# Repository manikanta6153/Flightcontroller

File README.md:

# Flight Controller PCB

A custom-designed flight controller board built around the **STM32F407VGT6** microcontroller, featuring a full 10-DOF IMU sensor suite (accelerometer, gyroscope, barometer, magnetometer), USB-C connectivity, and 16 Mbit onboard flash storage. Designed in **KiCad 10.0**.

---

##  Board Preview

### PCB Layout (3D Render)

### Schematic

---

## Key Features

- **MCU:** STM32F407VGT6 — ARM Cortex-M4 @ 168 MHz, 1 MB Flash, 192 KB RAM (LQFP-100)
- **IMU:** Bosch BMI323 — 6-axis accelerometer + gyroscope (SPI)
- **Barometer:** Bosch BMP390L — high-precision pressure/altitude sensor
- **Magnetometer:** MEMSIC MMC5983MA — 3-axis magnetic field sensor
- **Flash Memory:** Winbond W25Q16JVSS — 16 Mbit SPI NOR flash
- **Power:** LD3985M33R — 3.3 V LDO voltage regulator (SOT-23-5)
- **Interface:** USB Type-C 2.0 (16-pin receptacle)
- **ESD Protection:** SMAJ5.0A TVS diode on power input
- **6× Motor / Servo outputs** via JST-XH 2-pin connectors
- **Debug / Peripheral headers:** 1×5 pin and 1×3 pin (2.00 mm pitch)
- **Status LED** and **2× Tactile switches** (BOOT / RESET)
- **Crystal oscillator** — SMD 2016 package (HSE for STM32)

---

## Connectors

| Ref | Connector | Type | Purpose |
|-----|-----------|------|---------|
| J1  | USB Type-C 16P | Palconn UTC16-G | USB 2.0 data + power |
| J2  | 1×05 Pin Header | 2.00 mm pitch | Debug / UART / SWD |
| J3  | 1×03 Pin Header | 2.00 mm pitch | Peripheral (e.g. GPS / RX) |
| J4–J9 | JST-XH 2-pin (×6) | 2.50 mm pitch | Motor / Servo / ESC outputs |

---

## PCB Specifications

| Parameter | Value |
|-----------|-------|
| Layers | 2 (F.Cu + B.Cu) |
| Board Thickness | 1.6 mm |
| Copper Thickness | 35 µm |
| Substrate | FR4 (εr = 4.5) |
| Smallest SMD Package | 0201 (0603 Metric) |
| Design Tool | KiCad 10.0.3 |

---

## Bill of Materials (Summary)

| Category | Components | Details |
|----------|------------|---------|
| MCU | U1 — STM32F407VGT6 | LQFP-100 |
| IMU | U2 — BMI323 | 6-axis accel + gyro |
| LDO | U3 — LD3985M33R | 3.3 V regulator |
| Barometer | U4 — BMP390L | Pressure / altitude |
| Magnetometer | U5 — MMC5983MA | 3-axis compass |
| Flash | U7 — W25Q16JVSS | 16 Mbit SPI NOR |
| Capacitors | C1–C23 (23 total) | 12 pF – 10 µF, 0402–0805 |
| Resistors | R1–R19 (17 total) | 22 Ω – 100 kΩ, 0201–0805 |
| Diodes | D1 (LED), D2 (TVS) | Status indicator + ESD |
| Crystal | Y1 | SMD 2016, 4-pin |
| Ferrite Bead | FB1 — 600 Ω | EMI filtering (0201) |
| Switches | SW1, SW2 | SPST tactile (BOOT / RESET) |
| Connectors | J1–J9 | USB-C, pin headers, JST-XH |

> **Total unique part count:** ~31 line items &nbsp;|&nbsp; **Total components:** ~65+

---

## Project Structure

```
Flightcontroller/
├── flight.kicad_pro          # KiCad project file
├── flight.kicad_sch          # Schematic
├── flight.kicad_pcb          # PCB layout
├── flight.kicad_prl          # Local project preferences
├── flight.csv                # BOM export
├── flight.xml                # Netlist / BOM XML export
├── place_footprints.log      # Footprint placement log
└── README.md                 # This file
```

---

## Getting Started

### Prerequisites
- [KiCad 10.0+](https://www.kicad.org/download/) installed

### Open the Project
1. Clone or download this repository
2. Open `flight.kicad_pro` in KiCad
3. Use the Schematic Editor to view/edit the circuit
4. Use the PCB Editor to view/edit the board layout

```bash
git clone https://github.com/manikanta6153/Flightcontroller.git
cd Flightcontroller
```

---

## Sensor Communication Interfaces

| Sensor | IC | Interface | Notes |
|--------|----|-----------|-------|
| Accel + Gyro | BMI323 | SPI | 6-axis IMU |
| Barometer | BMP390L | SPI / I²C | Altitude estimation |
| Magnetometer | MMC5983MA | SPI / I²C | Heading / compass |
| Flash | W25Q16JVSS | SPI | Blackbox / config storage |

---

## License

This is an open hardware project. See the repository for license details.

---

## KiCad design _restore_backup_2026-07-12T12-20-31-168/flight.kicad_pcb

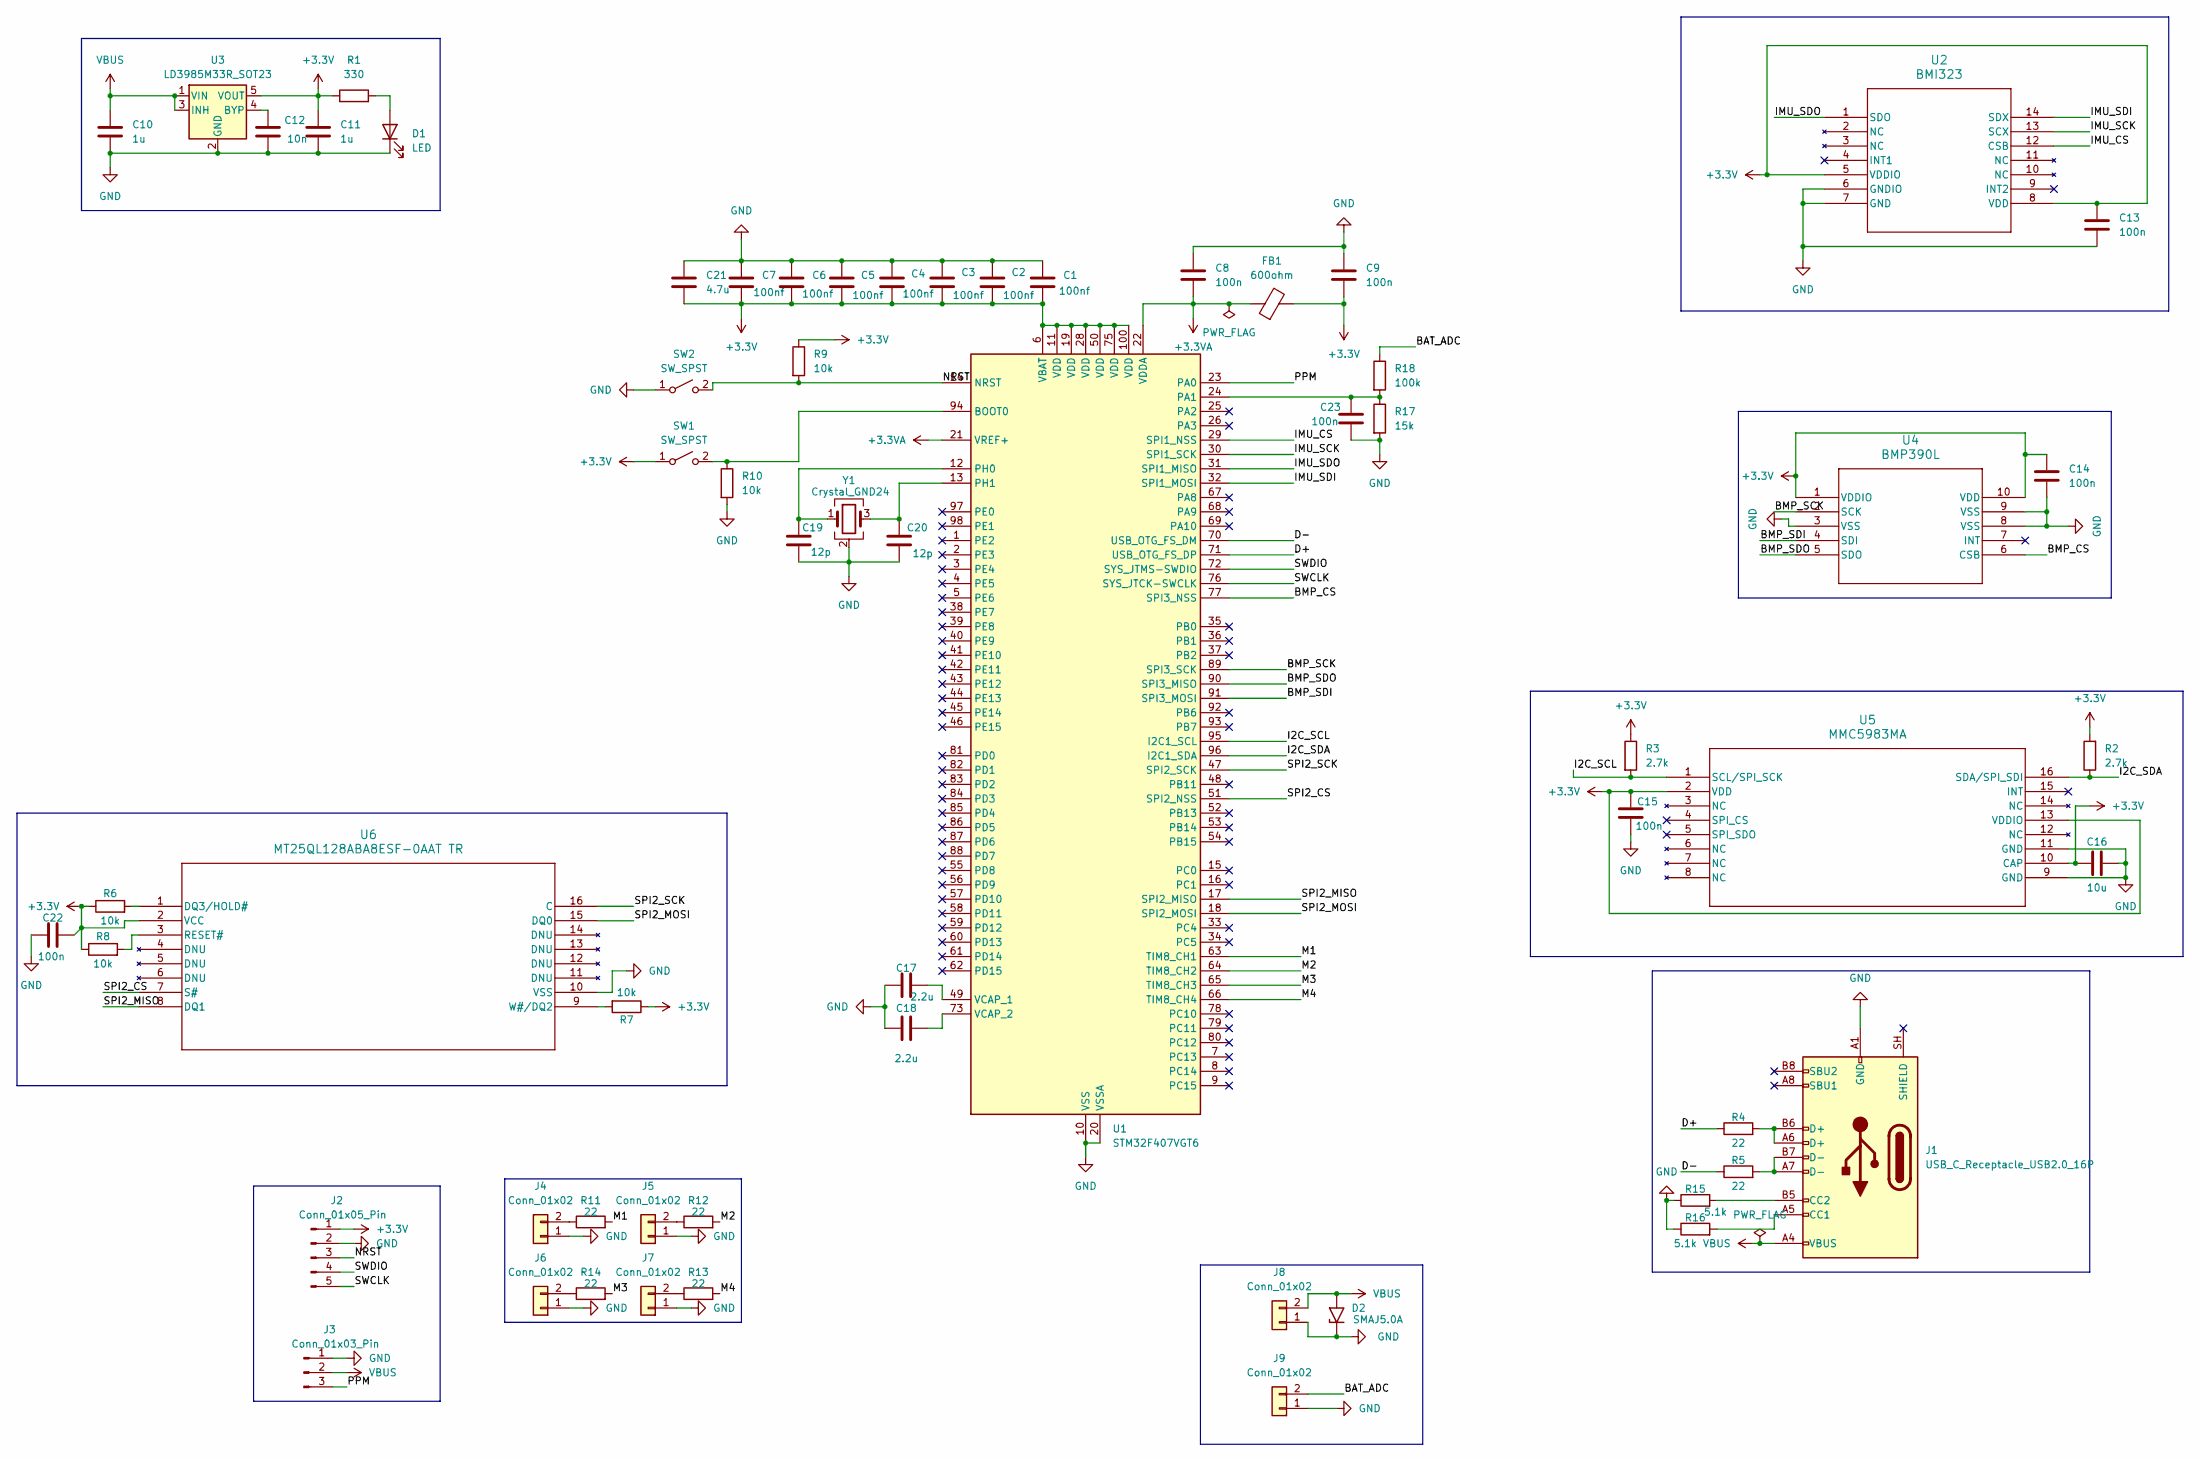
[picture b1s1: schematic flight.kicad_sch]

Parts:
C1, C2, C3, C4, C5, C6, C7: 100nf; C_0603_1608Metric
C8, C9, C13, C14, C15, C22, C23: 100n; C_0603_1608Metric
C10, C11: 1u; C_0603_1608Metric
C12: 10n; C_0805_2012Metric
C16: 10u; C_0402_1005Metric
C17, C18: 2.2u; C_0805_2012Metric
C19, C20: 12p; C_0402_1005Metric
C21: 4.7u; C_0805_2012Metric
D1: LED; C_0805_2012Metric
D2: SMAJ5.0A; D_SMA
FB1: 600ohm; L_0201_0603Metric
J1: USB_C_Receptacle_USB2.0_16P; USB_C_Receptacle_Palconn_UTC16-G
J2: Conn_01x05_Pin; PinHeader_1x05_P2.00mm_Vertical
J3: Conn_01x03_Pin; PinHeader_1x03_P2.00mm_Vertical
J4, J5, J6, J7, J8, J9: Conn_01x02; JST_XH_B2B-XH-A_1x02_P2.50mm_Vertical
R1: 330; R_0603_1608Metric
R2, R3: 2.7k; R_0805_2012Metric
R4, R5, R11, R12, R13, R14: 22; R_0603_1608Metric
R6, R7, R8, R9, R10: 10k; R_0603_1608Metric
R15, R16: 5.1k; R_0201_0603Metric
R17: 15k; R_0805_2012Metric
R18: 100k; R_0805_2012Metric
SW1, SW2: SW_SPST; SW_SPST_TS-1088-xR025
U1: STM32F407VGT6; LQFP-100_14x14mm_P0.5mm
U2: BMI323; XDCR_BMI270
U3: LD3985M33R_SOT23; SOT-23-5
U4: BMP390L; 10LGA_2X2X0p75_BOS-L
U5: MMC5983MA; MMC5983MA_MEM
U6: MT25QL128ABA8ESF-0AAT TR; SOP2_300MILS_SF_MRN
Y1: Crystal_GND24; Crystal_SMD_2016-4Pin_2.0x1.6mm

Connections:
+3.3V: C1.2, C2.2, C3.2, C4.2, C5.2, C6.2, C7.2, C9.2, C11.1, C13.1, C14.1, C15.1, C16.1, C21.2, C22.2, FB1.2, J2.1, R1.1, R2.2, R3.1, R6.1, R7.1, R8.1, R9.1, SW1.1 (A), U1.6 (VBAT), U1.11 (VDD), U1.19 (VDD), U1.28 (VDD), U1.50 (VDD), U1.75 (VDD), U1.100 (VDD), U2.5 (VDDIO), U2.8 (VDD), U3.5 (VOUT), U4.1 (VDDIO), U4.10 (VDD), U5.2 (VDD), U5.10 (CAP), U5.13 (VDDIO), U6.2 (VCC)
+3.3VA: C8.2, FB1.1, U1.21 (VREF+), U1.22 (VDDA)
/BAT_ADC: J9.2, R18.1
/BMP_CS: U1.77 (SPI3_NSS), U4.6 (CSB)
/BMP_SCK: U1.89 (SPI3_SCK), U4.2 (SCK)
/BMP_SDI: U1.91 (SPI3_MOSI), U4.4 (SDI)
/BMP_SDO: U1.90 (SPI3_MISO), U4.5 (SDO)
/D+: R4.1, U1.71 (USB_OTG_FS_DP)
/D-: R5.1, U1.70 (USB_OTG_FS_DM)
/I2C_SCL: R3.2, U1.95 (I2C1_SCL), U5.1 (SCL/SPI_SCK)
/I2C_SDA: R2.1, U1.96 (I2C1_SDA), U5.16 (SDA/SPI_SDI)
/IMU_CS: U1.29 (SPI1_NSS), U2.12 (CSB)
/IMU_SCK: U1.30 (SPI1_SCK), U2.13 (SCX)
/IMU_SDI: U1.32 (SPI1_MOSI), U2.14 (SDX)
/IMU_SDO: U1.31 (SPI1_MISO), U2.1 (SDO)
/M1: R11.2, U1.63 (TIM8_CH1)
/M2: R12.2, U1.64 (TIM8_CH2)
/M3: R14.2, U1.65 (TIM8_CH3)
/M4: R13.2, U1.66 (TIM8_CH4)
/NRST: J2.3, R9.2, SW2.2 (B), U1.14 (NRST)
/PPM: J3.3, U1.23 (PA0)
/SPI2_CS: U1.51 (SPI2_NSS), U6.7 (S#)
/SPI2_MISO: U1.17 (SPI2_MISO), U6.8 (DQ1)
/SPI2_MOSI: U1.18 (SPI2_MOSI), U6.15 (DQ0)
/SPI2_SCK: U1.47 (SPI2_SCK), U6.16 (C)
/SWCLK: J2.5, U1.76 (SYS_JTCK-SWCLK)
/SWDIO: J2.4, U1.72 (SYS_JTMS-SWDIO)
GND: C1.1, C2.1, C3.1, C4.1, C5.1, C6.1, C7.1, C8.1, C9.1, C10.2, C11.2, C12.2, C13.2, C14.2, C15.2, C16.2, C17.1, C18.1, C19.2, C20.2, C21.1, C22.1, C23.2, D1.1 (K), D2.1 (A1), J1.A1 (GND), J1.A12 (GND), J1.B1 (GND), J1.B12 (GND), J2.2, J3.1, J4.1, J5.1, J6.1, J7.1, J8.1, J9.1, R10.2, R15.1, R16.1, R17.2, SW2.1 (A), U1.10 (VSS), U1.20 (VSSA), U1.27 (VSS), U1.74 (VSS), U1.99 (VSS), U2.6 (GNDIO), U2.7 (GND), U3.2 (GND), U4.3 (VSS), U4.8 (VSS), U4.9 (VSS), U5.9 (GND), U5.11 (GND), U6.10 (VSS), Y1.2 (G), Y1.4 (G)
unnamed: D1.2 (A), R1.2
unnamed: J1.A5 (CC1), R16.2
unnamed: J1.B5 (CC2), R15.2
unnamed: J1.A6 (D+), J1.B6 (D+), R4.2
unnamed: J1.A7 (D-), J1.B7 (D-), R5.2
unnamed: J4.2, R11.1
unnamed: J5.2, R12.1
unnamed: J6.2, R14.1
unnamed: J7.2, R13.1
unnamed: R10.1, SW1.2 (B), U1.94 (BOOT0)
unnamed: C23.1, R17.1, R18.2, U1.24 (PA1)
unnamed: C19.1, U1.12 (PH0), Y1.1
unnamed: C20.1, U1.13 (PH1), Y1.3
unnamed: C17.2, U1.49 (VCAP_1)
unnamed: C18.2, U1.73 (VCAP_2)
unnamed: C12.1, U3.4 (BYP)
unnamed: R6.2, U6.1 (DQ3/HOLD#)
unnamed: R8.2, U6.3 (RESET#)
unnamed: R7.2, U6.9 (W#/DQ2)
VBUS: C10.1, D2.2 (A2), J1.A4 (VBUS), J1.A9 (VBUS), J1.B4 (VBUS), J1.B9 (VBUS), J3.2, J8.2, U3.1 (VIN), U3.3 (INH)

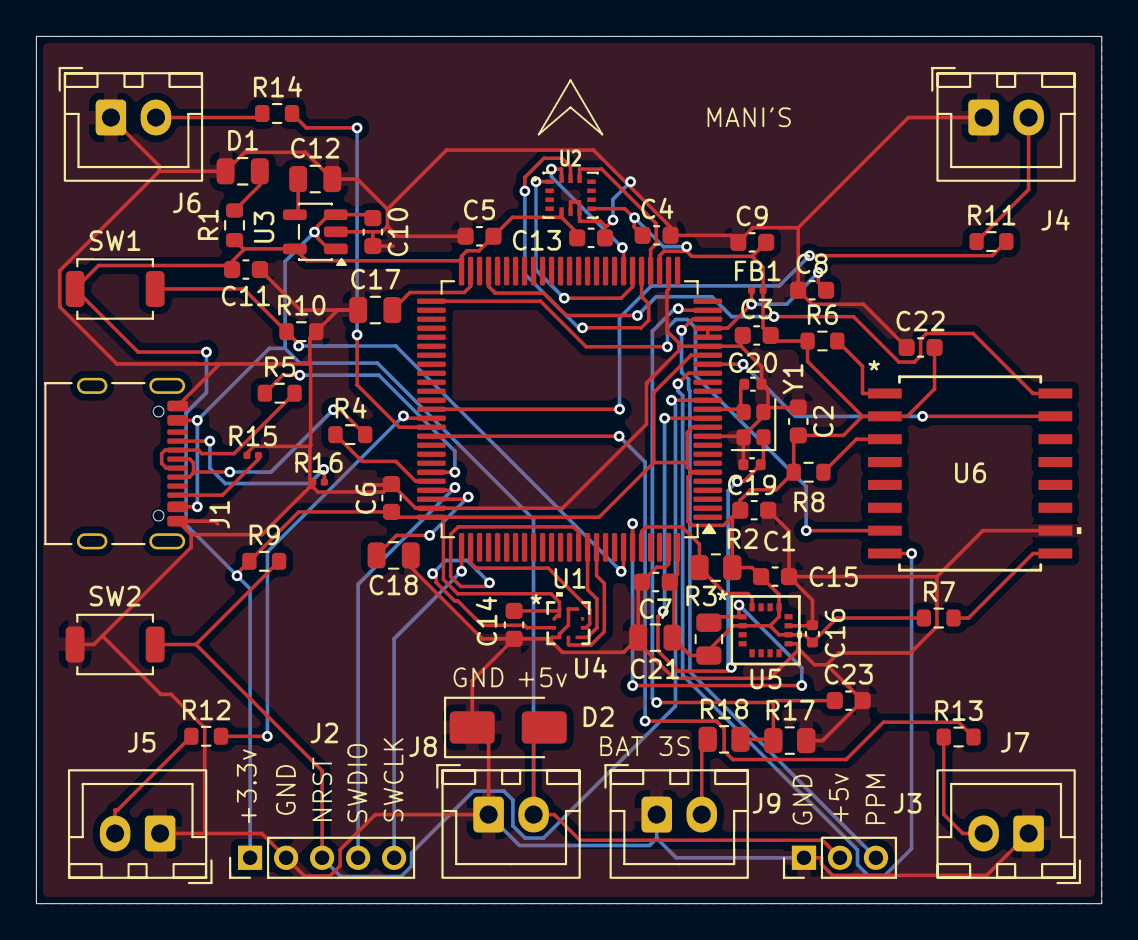
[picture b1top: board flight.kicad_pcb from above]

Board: 2 copper layers, 59.2 x 48.2 mm, 62 parts (0 on the bottom side), 48 nets.
